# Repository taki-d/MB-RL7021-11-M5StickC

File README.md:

# MB-RL7021-11-M5StickC

Firmware backup and build troubleshooting notes are in
[`docs/firmware-dump-and-build-notes.md`](docs/firmware-dump-and-build-notes.md).

## Firmware configuration

Create `firmware/src/credentials.h` (it is intentionally ignored by Git) and
set the Wi-SUN and Wi-Fi credentials:

```cpp
String bid = "XXXXXXXXXXXXXXXXXXXXXXXXXXXXXXXX";
String bpass = "XXXXXXXXXXXX";
const char *ssid = "your-wifi-ssid";
const char *password = "your-wifi-password";
```

The firmware starts Wi-Fi and the RL7023 state machine independently. UART
responses are consumed from `loop()` without blocking delays, so the HTTP
server remains responsive while scanning, joining, or retrying the module.

Endpoints:

- `/metrics` — Prometheus-compatible power, current, and cumulative-energy metrics
- `/healthz` — `200` when Wi-Fi and the meter session are connected, including response waits
- `/` — short status summary

Enable or disable each metric and adjust its polling interval in
`firmware/src/metrics_config.h` and rebuild. Power has a 1-second minimum
request interval; measured sequential responses arrive about every 2–2.4 seconds
on the tested meter. Current is disabled by default to prioritize power updates;
set `kEnableInstantaneousCurrent = true` to restore its requests and metrics.
Cumulative-energy requests remain enabled every 30 minutes and take turns on
the same transport, temporarily extending that period. If current is enabled,
E7+E8 are requested together every 30 seconds (typically about 4.4 seconds on
this meter). Occasional reply delays caused 7–8.5-second sample gaps in earlier
testing; these intervals are not hard upper bounds. Slow energy requests are
interleaved with power instead of queued in a batch. `kCombinePowerAndCurrent`
can disable the combined request; a rejection or timeout automatically falls
back to separate requests for that boot.

`kEnablePowerTimingMetrics` exposes received-sample age, the latest sample gap,
and a sample counter alongside power. Timing traces and a repeatable measurement
script are documented in [the latency investigation](docs/polling-latency-2026-10-07.md).

## On-device display

The landscape 240×135 display shows large, width-adjusted watts, Wi-Fi status,
and a time-based two-minute power trend. `RX` is the age of the last received
sample; `DT` is the interval between the last two samples. `DELAY` (5 seconds)
and `STALE` (10 seconds) distinguish an old reading from a live one. Connection
progress is shown before the first sample; an unknown value is never shown as zero.

The framebuffer is reused and only changed 16-row strips are transferred, one
per loop iteration, so drawing does not block UART servicing for a full frame.
See [display details and tests](docs/display-improvements-2026-10-07.md).

## Tests and continuous integration

[Firmware CI](https://github.com/taki-d/MB-RL7021-11-M5StickC/actions/workflows/ci.yml)
runs on pushes, pull requests, and manual dispatch:

- Protocol parser, transaction/fallback tests, and Python capture-window tests.
- An ESP32 firmware build with public dummy credentials, followed by display
  layout, history, rollover, and allocation-failure tests.
- Both C++ suites run with AddressSanitizer and UndefinedBehaviorSanitizer.
  Synthetic display previews are retained as PPM artifacts for seven days.

No device, real credentials, or GitHub Secrets are needed. CI never uploads to
hardware and never publishes firmware binaries or flash dumps. It does not
replace the physical meter latency and LCD checks documented above.

To run the same tests locally:

```sh
bash scripts/run_host_tests.sh core
# Install the M5 font dependency once before running the display tests:
pio pkg install -d firmware -e m5stick-c
bash scripts/run_host_tests.sh display
# Or run both suites:
bash scripts/run_host_tests.sh
```

The script supports `CXX`, `PYTHON`, and `TEST_BUILD_DIR` overrides. Output goes
to the ignored `.pio/host-tests` directory by default. Keep your local
`firmware/src/credentials.h`; the CI dummy header is only for clean CI runners.
PlatformIO Core is pinned in `tests/ci/requirements.txt`; tested platform and
library versions are pinned in `firmware/platformio.ini`. Official actions are
pinned to release commit SHAs.

## VS Code IntelliSense

Open `MB-RL7021-11-M5StickC.code-workspace` with the PlatformIO IDE and
Microsoft C/C++ extensions enabled. The repository and firmware folder each
have `.vscode/settings.json`, so opening either folder directly also configures
C/C++ include lookup.

Generate the compilation database from the repository root in a PlatformIO
terminal:

```sh
pio run -d firmware -e m5stick-c -t compiledb
```

This installs the required PlatformIO packages and writes
`firmware/compile_commands.json`. IntelliSense reads the actual compiler,
include paths, and preprocessor definitions from that file. Regenerate it after
changing `platformio.ini` or adding source files or dependencies. The database
contains local absolute paths and is excluded from Git.

Before generation, the settings provide fallback paths for project headers and
downloaded project libraries. ESP32 framework headers require the packages and
compilation database; `credentials.h` must be created separately as described
above. If diagnostics persist after generation, run `C/C++: Reset IntelliSense
Database` from the command palette.

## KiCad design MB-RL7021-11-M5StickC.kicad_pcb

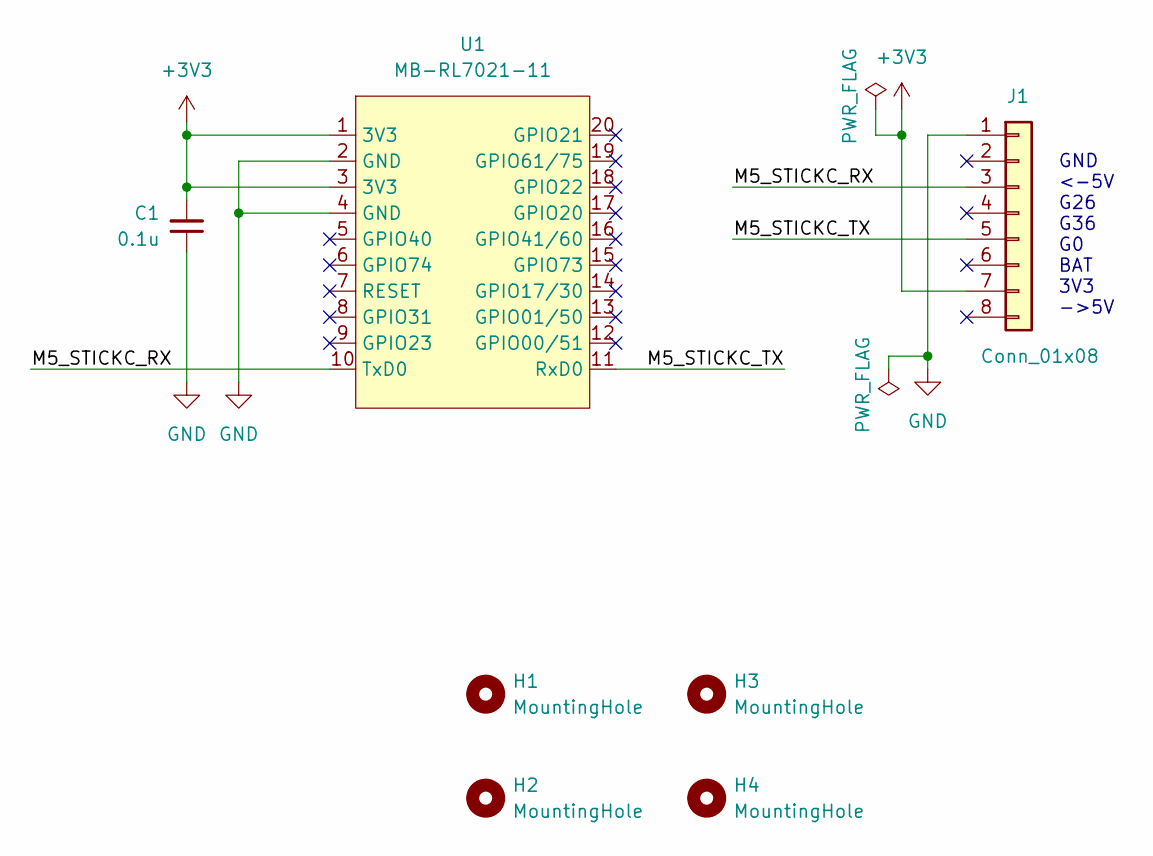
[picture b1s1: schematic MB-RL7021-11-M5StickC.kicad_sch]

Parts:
C1: 0.1u; C_0603_1608Metric
H1, H2, H3, H4: MountingHole; MountingHole_3.2mm_M3
J1: Conn_01x08; PinHeader_1x08_P2.54mm_Horizontal
U1: MB-RL7021-11

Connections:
+3V3: C1.2, J1.7, U1.1 (3V3), U1.3 (3V3)
/M5_STICKC_RX: J1.3, U1.10 (TxD0)
/M5_STICKC_TX: J1.5, U1.11 (RxD0)
GND: C1.1, J1.1, U1.2 (GND), U1.4 (GND)

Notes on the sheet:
GND <-5V G26 G36 G0 BAT 3V3 ->5V

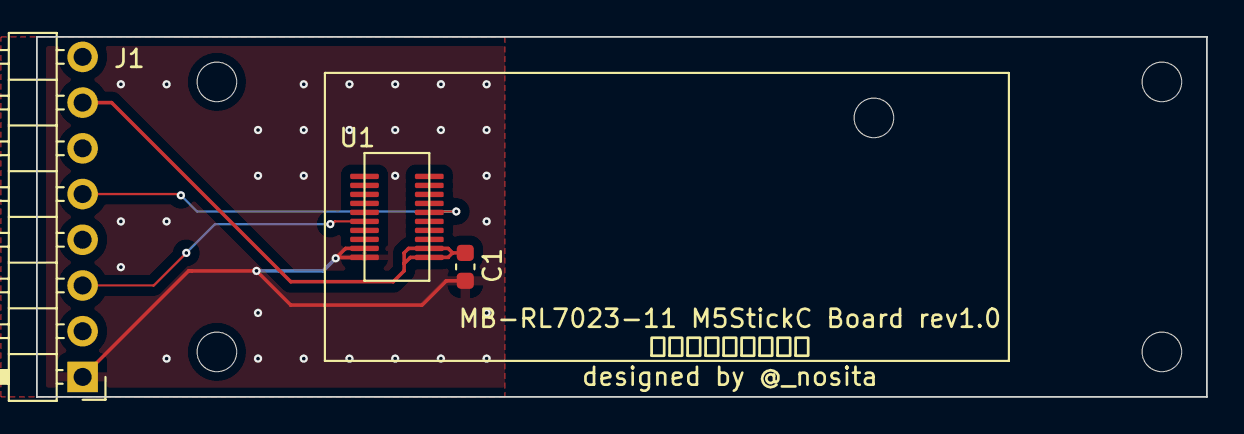
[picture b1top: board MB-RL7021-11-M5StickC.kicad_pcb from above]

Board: 2 copper layers, 65.0 x 20.0 mm, 7 parts (0 on the bottom side), 4 nets.

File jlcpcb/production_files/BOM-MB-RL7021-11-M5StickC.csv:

Comment,Designator,Footprint,LCSC
0.1u,C1,C_0603_1608Metric,C14663
Conn_01x08,J1,PinHeader_1x08_P2.54mm_Horizontal,C225494
MB-RL7021-11,U1,MB-RL7021-11,C2917815
MountingHole,H2,MountingHole_2.2mm_M2,
MountingHole,H4,MountingHole_2.2mm_M2,
MountingHole,H1,MountingHole_2.2mm_M2,
MountingHole,H3,MountingHole_2.2mm_M2,

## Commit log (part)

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2023-04-01 Add: add firmware
2023-04-01 Update: update gitignore
2023-04-01 Add: add board directory
2023-04-01 Update: update readme
2023-04-01 Add: add metrics export server
2023-08-14 rev1.2 穴のシルクを消した．
2023-08-14 temporary commit
2023-08-14 v1.0 モジュール固定用の穴の位置を調整
2023-08-14 ver1.1 ねじをm2に変更
2023-08-14 Add: add project
